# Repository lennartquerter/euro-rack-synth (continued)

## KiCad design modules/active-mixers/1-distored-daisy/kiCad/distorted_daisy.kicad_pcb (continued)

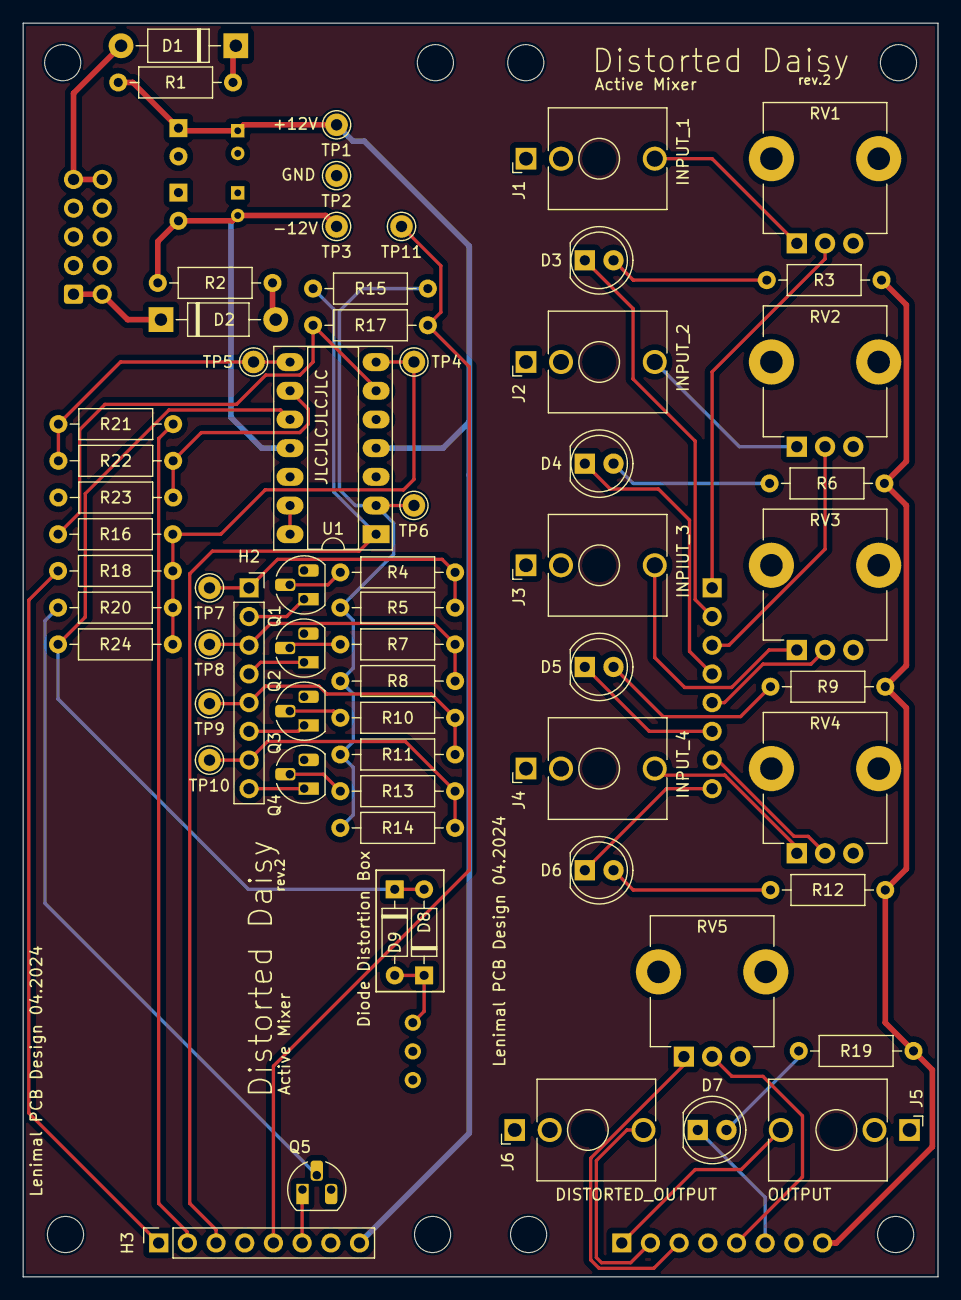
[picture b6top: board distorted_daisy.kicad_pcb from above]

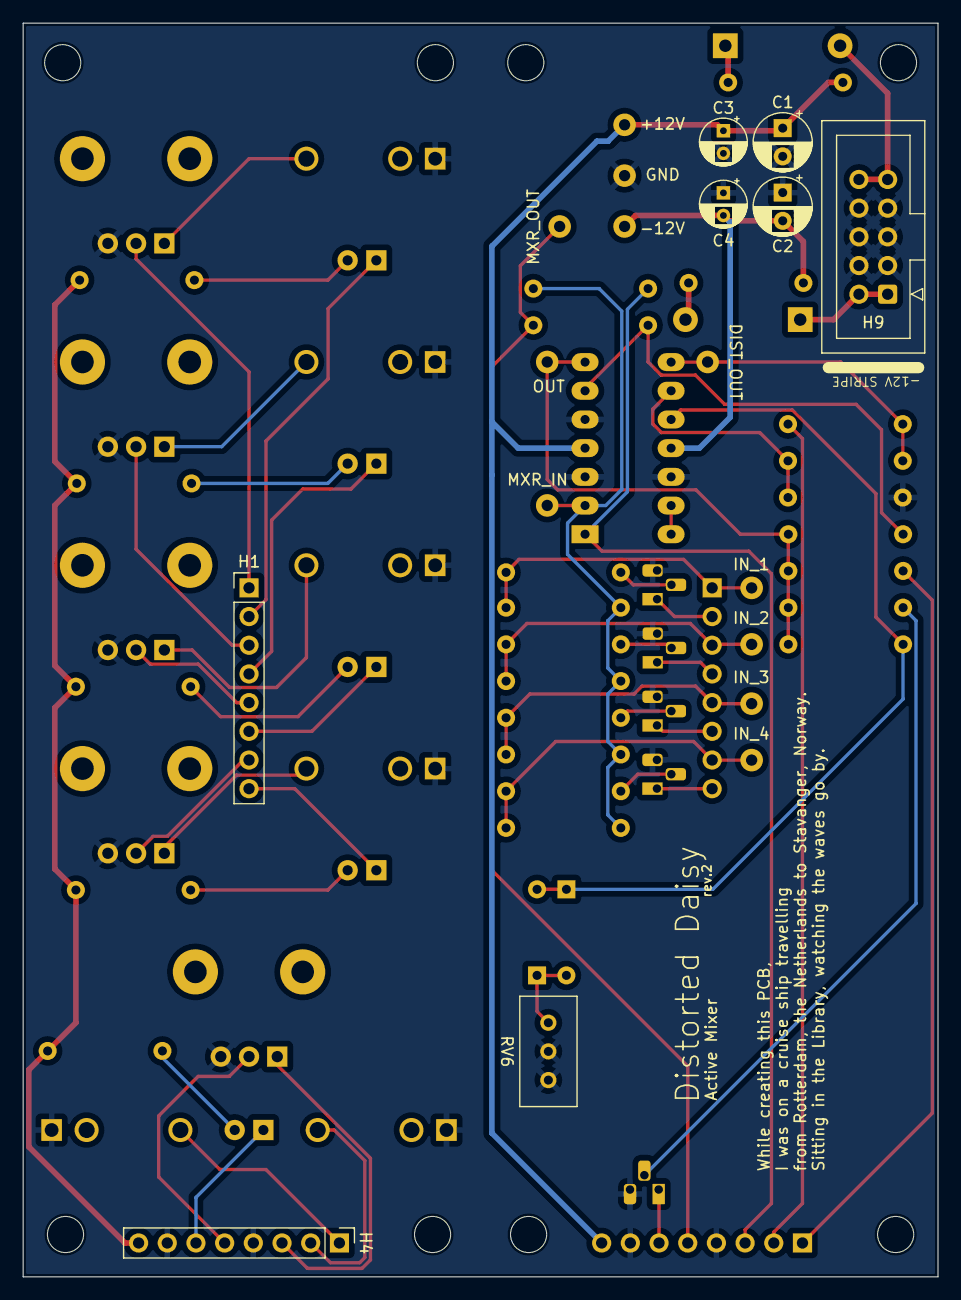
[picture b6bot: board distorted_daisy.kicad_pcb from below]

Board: 2 copper layers, 81.0 x 111.0 mm, 79 parts (8 on the bottom side), 55 nets.

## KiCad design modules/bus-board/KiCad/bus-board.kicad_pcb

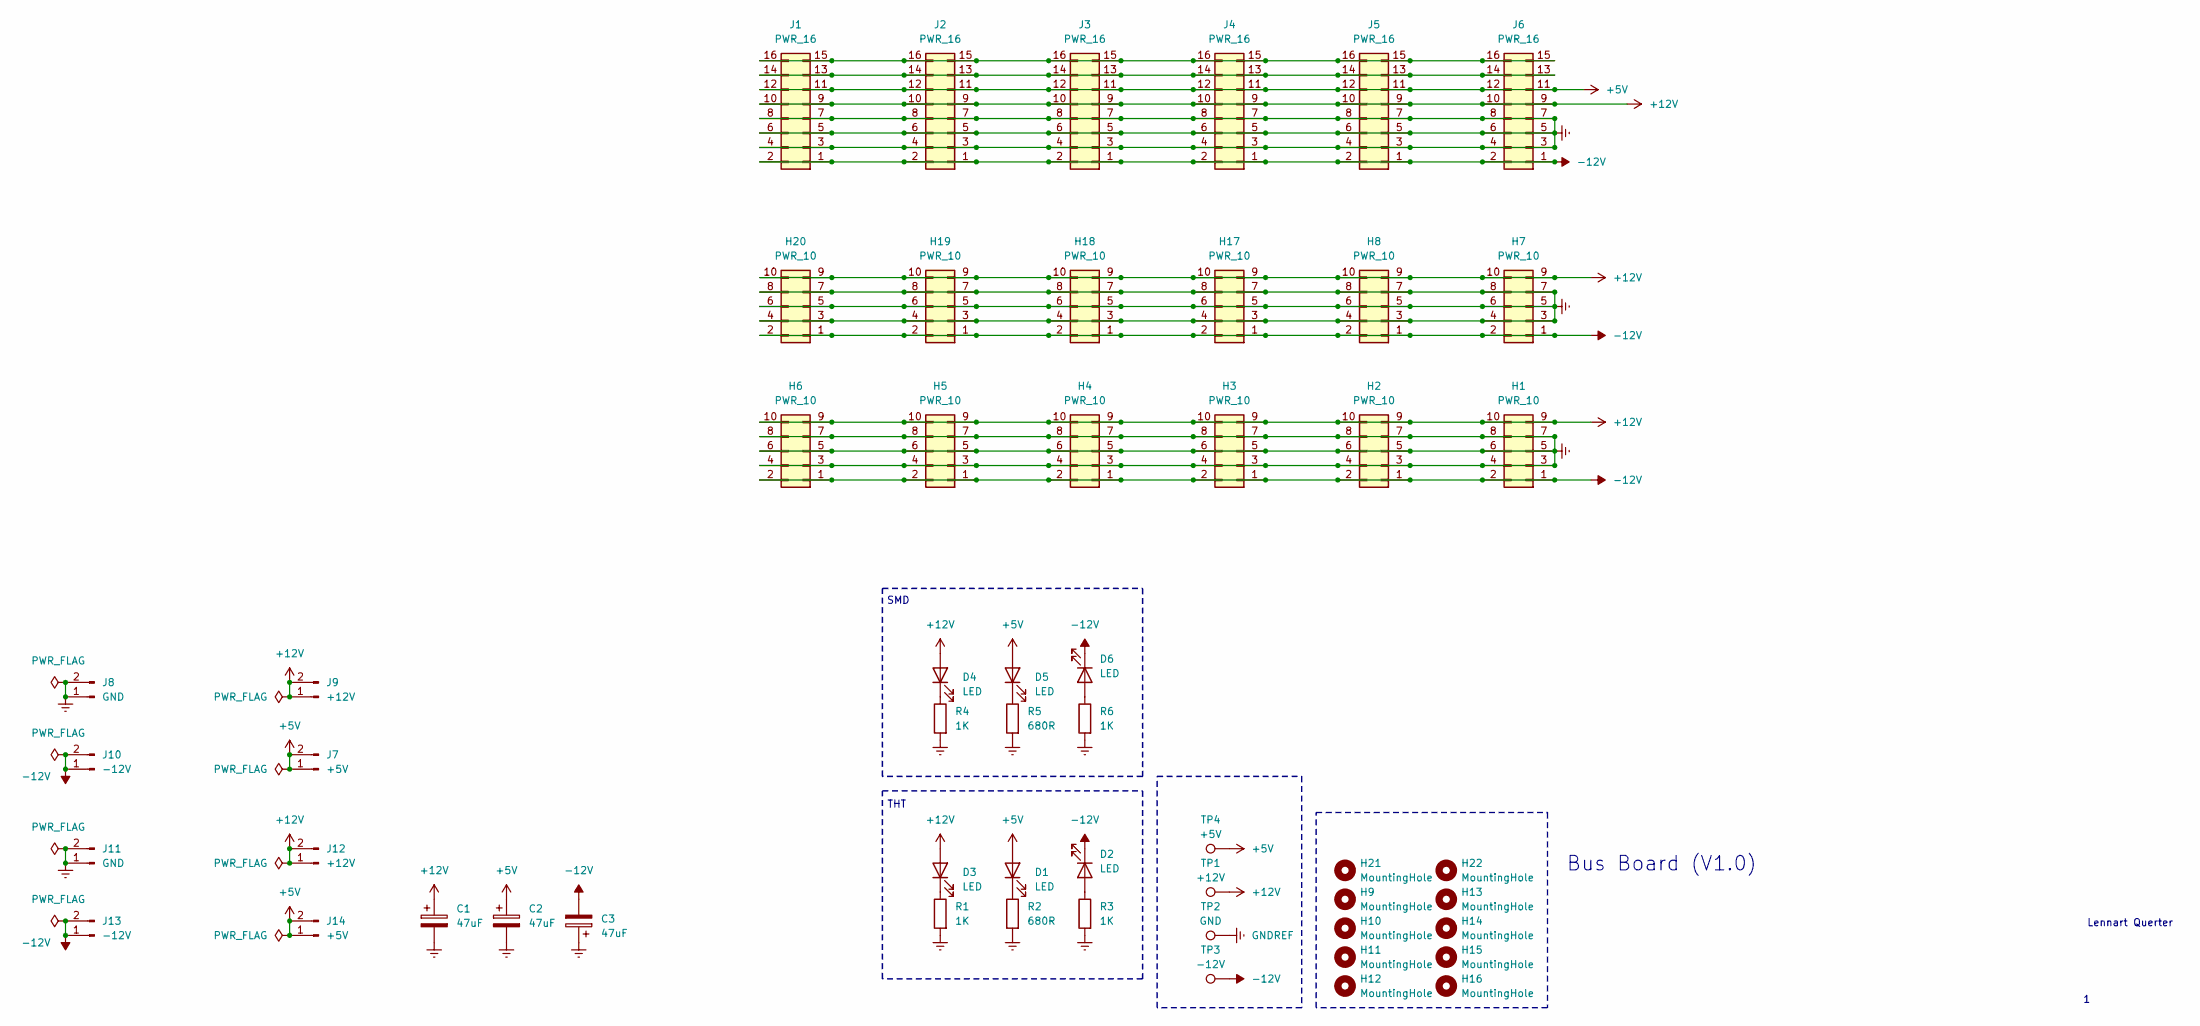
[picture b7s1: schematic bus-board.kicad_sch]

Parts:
C1, C2, C3: 47uF; CP_Radial_D6.3mm_P2.50mm
D1, D2, D3: LED; LED_D3.0mm
D4, D5, D6: LED; LED_0805_2012Metric_Pad1.15x1.40mm_HandSolder
H1, H2, H3, H4, H5, H6, H7, H8, H17, H18, H19, H20: PWR_10; IDC-Header_2x05_P2.54mm_Vertical
H9, H10, H11, H12, H13, H14, H15, H16, H21, H22: MountingHole; MountingHole_3.2mm_M3
J1, J2, J3, J4, J5, J6: PWR_16; IDC-Header_2x08_P2.54mm_Vertical
J7, J14: +5V; power-socket
J8, J11: GND; power-socket
J9, J12: +12V; power-socket
J10, J13: -12V; power-socket
R1, R3: 1K; R_Default (DIN0207)
R2: 680R; R_Default (DIN0207)
R4, R6: 1K; R_0805_2012Metric_Pad1.20x1.40mm_HandSolder
R5: 680R; R_0805_2012Metric_Pad1.20x1.40mm_HandSolder
TP1: +12V; Pin_D1.0mm_L10.0mm
TP2: GND; Pin_D1.0mm_L10.0mm
TP3: -12V; Pin_D1.0mm_L10.0mm
TP4: +5V; Pin_D1.0mm_L10.0mm

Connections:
+5V: C2.1, D1.2 (A), D5.2 (A), J1.11 (+5V), J1.12 (+5V), J2.11 (+5V), J2.12 (+5V), J3.11 (+5V), J3.12 (+5V), J4.11 (+5V), J4.12 (+5V), J5.11 (+5V), J5.12 (+5V), J6.11 (+5V), J6.12 (+5V), J7.1, J7.2, J14.1, J14.2, TP4.1 (1_1)
+12V: C1.1, D3.2 (A), D4.2 (A), H1.9, H1.10, H2.9, H2.10, H3.9, H3.10, H4.9, H4.10, H5.9, H5.10, H6.9, H6.10, H7.9, H7.10, H8.9, H8.10, H17.9, H17.10, H18.9, H18.10, H19.9, H19.10, H20.9, H20.10, J1.9 (+12V), J1.10 (+12V), J2.9 (+12V), J2.10 (+12V), J3.9 (+12V), J3.10 (+12V), J4.9 (+12V), J4.10 (+12V), J5.9 (+12V), J5.10 (+12V), J6.9 (+12V), J6.10 (+12V), J9.1, J9.2, J12.1, J12.2, TP1.1 (1_1)
-12V: C3.2, D2.1 (K), D6.1 (K), H1.1, H1.2, H2.1, H2.2, H3.1, H3.2, H4.1, H4.2, H5.1, H5.2, H6.1, H6.2, H7.1, H7.2, H8.1, H8.2, H17.1, H17.2, H18.1, H18.2, H19.1, H19.2, H20.1, H20.2, J1.1 (-12V), J1.2 (-12V), J2.1 (-12V), J2.2 (-12V), J3.1 (-12V), J3.2 (-12V), J4.1 (-12V), J4.2 (-12V), J5.1 (-12V), J5.2 (-12V), J6.1 (-12V), J6.2 (-12V), J10.1, J10.2, J13.1, J13.2, TP3.1 (1_1)
GNDREF: C1.2, C2.2, C3.1, H1.3, H1.4, H1.5, H1.6, H1.7, H1.8, H2.3, H2.4, H2.5, H2.6, H2.7, H2.8, H3.3, H3.4, H3.5, H3.6, H3.7, H3.8, H4.3, H4.4, H4.5, H4.6, H4.7, H4.8, H5.3, H5.4, H5.5, H5.6, H5.7, H5.8, H6.3, H6.4, H6.5, H6.6, H6.7, H6.8, H7.3, H7.4, H7.5, H7.6, H7.7, H7.8, H8.3, H8.4, H8.5, H8.6, H8.7, H8.8, H17.3, H17.4, H17.5, H17.6, H17.7, H17.8, H18.3, H18.4, H18.5, H18.6, H18.7, H18.8, H19.3, H19.4, H19.5, H19.6, H19.7, H19.8, H20.3, H20.4, H20.5, H20.6, H20.7, H20.8, J1.3 (GND), J1.4 (GND), J1.5 (GND), J1.6 (GND), J1.7 (GND), J1.8 (GND), J2.3 (GND), J2.4 (GND), J2.5 (GND), J2.6 (GND), J2.7 (GND), J2.8 (GND), J3.3 (GND), J3.4 (GND), J3.5 (GND), J3.6 (GND), J3.7 (GND), J3.8 (GND), J4.3 (GND), J4.4 (GND), J4.5 (GND), J4.6 (GND), J4.7 (GND), J4.8 (GND), J5.3 (GND), J5.4 (GND), J5.5 (GND), J5.6 (GND), J5.7 (GND), J5.8 (GND), J6.3 (GND), J6.4 (GND), J6.5 (GND), J6.6 (GND), J6.7 (GND), J6.8 (GND), J8.1, J8.2, J11.1, J11.2, R1.1, R2.1, R3.1, R4.1, R5.1, R6.1, TP2.1 (1_1)
unnamed: D1.1 (K), R2.2
unnamed: D2.2 (A), R3.2
unnamed: D3.1 (K), R1.2
unnamed: D4.1 (K), R4.2
unnamed: D5.1 (K), R5.2
unnamed: D6.2 (A), R6.2
unnamed: J1.13 (CV), J1.14 (CV), J2.13 (CV), J2.14 (CV), J3.13 (CV), J3.14 (CV), J4.13 (CV), J4.14 (CV), J5.13 (CV), J5.14 (CV), J6.13 (CV), J6.14 (CV)
unnamed: J1.15 (GATE), J1.16 (GATE), J2.15 (GATE), J2.16 (GATE), J3.15 (GATE), J3.16 (GATE), J4.15 (GATE), J4.16 (GATE), J5.15 (GATE), J5.16 (GATE), J6.15 (GATE), J6.16 (GATE)

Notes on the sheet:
THT
SMD
Bus Board (V1.0)
Lennart Querter

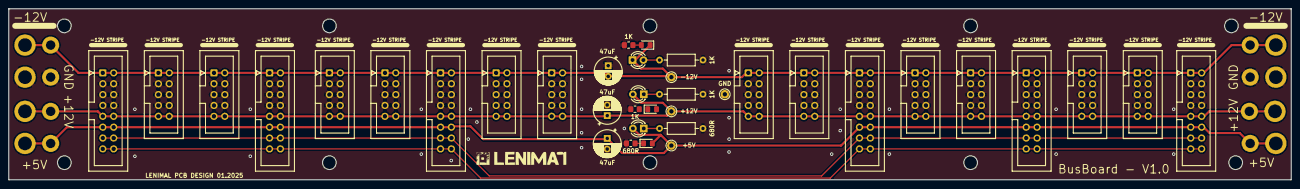
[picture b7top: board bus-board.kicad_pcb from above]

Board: 2 copper layers, 300.0 x 40.0 mm, 55 parts (0 on the bottom side), 12 nets.

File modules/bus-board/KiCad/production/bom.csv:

Designator,Footprint,Quantity,Value,LCSC Part #
"C1, C2, C3",CP_Radial_D6.3mm_P2.50mm,3,47uF,
"D1, D2, D3",LED_D3.0mm,3,LED,
"D4, D5, D6",0805,3,LED,
"H1, H17, H18, H19, H2, H20, H3, H4, H5, H6, H7, H8",IDC-Header_2x05_P2.54mm_Vertical,12,PWR_10,
"J1, J2, J3, J4, J5, J6",IDC-Header_2x08_P2.54mm_Vertical,6,PWR_16,
"J10, J13",power-socket,2,-12V,
"J11, J8",power-socket,2,GND,
"J12, J9",power-socket,2,+12V,
"J14, J7",power-socket,2,+5V,
"R1, R3",R_Default (DIN0207),2,1K,
R2,R_Default (DIN0207),1,680R,
"R4, R6",0805,2,1K,
R5,0805,1,680R,
